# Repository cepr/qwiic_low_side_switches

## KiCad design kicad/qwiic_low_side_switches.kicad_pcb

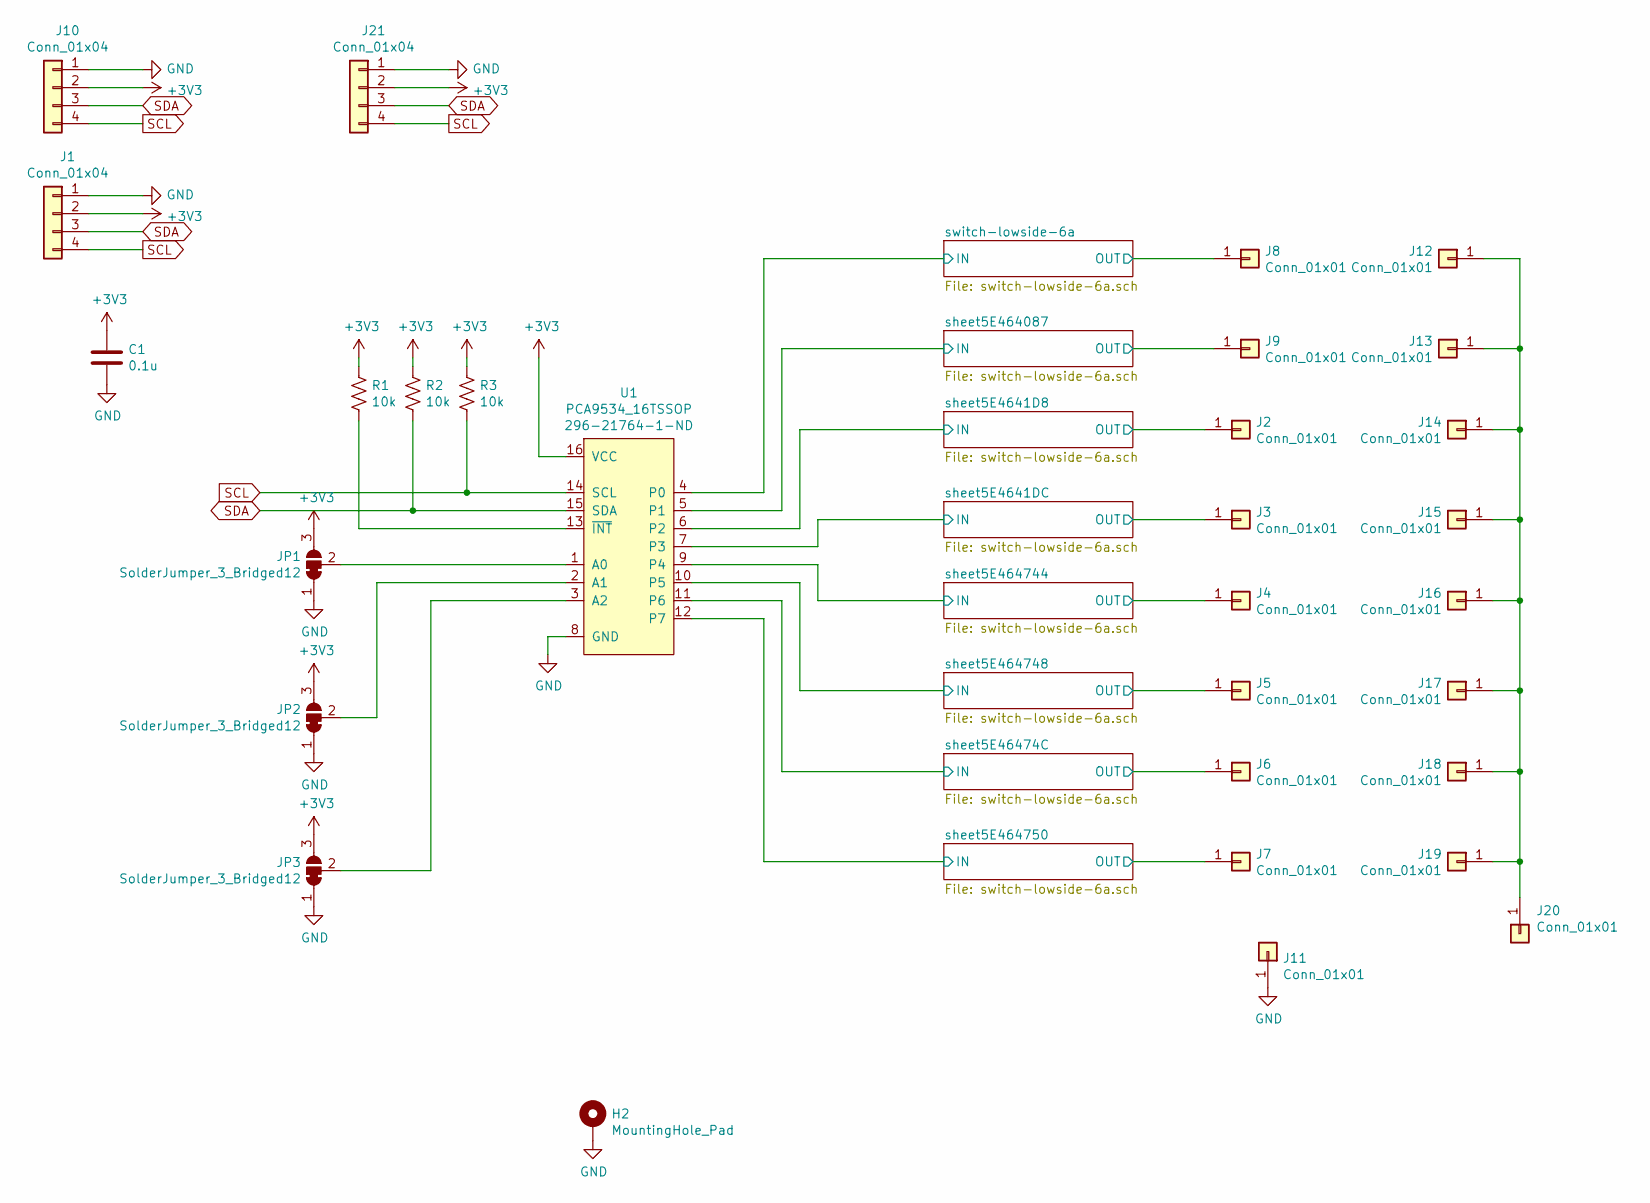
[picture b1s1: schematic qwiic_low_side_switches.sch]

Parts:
C1: 0.1u; C_0805_2012Metric_Pad1.15x1.40mm_HandSolder; DigiKey 478-6048-1-ND
H2: MountingHole_Pad; MountingHole_3.2mm_M3_Pad_Via
J1, J10: Conn_01x04; JST_SH_SM04B-SRSS-TB_1x04-1MP_P1.00mm_Horizontal; DigiKey 455-1804-1-ND
J2, J3, J4, J5, J6, J7, J8, J9, J11, J12, J13, J14, J15, J16, J17, J18, J19, J20: Conn_01x01; TestPoint_Pad_4.0x4.0mm
J21: Conn_01x04; PinSocket_1x04_P1.27mm_Vertical
JP1, JP2, JP3: SolderJumper_3_Bridged12; SolderJumper-3_P1.3mm_Bridged12_RoundedPad1.0x1.5mm_NumberL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
R1, R2, R3: 10k; R_0805_2012Metric_Pad1.15x1.40mm_HandSolder; DigiKey 311-10.0KCRCT-ND
U1: PCA9534_16TSSOP; TSSOP-16_4.4x5mm_P0.65mm; DigiKey 296-21764-1-ND

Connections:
+3V3: C1.1, J1.2, J10.2, J21.2, JP1.3 (B), JP2.3 (B), JP3.3 (B), R1.1, R2.1, R3.1, U1.16 (VCC)
/sheet5E4641D8/IN: U1.6 (P2); also elsewhere on the board
/sheet5E4641D8/OUT: J2.1; also elsewhere on the board
/sheet5E4641DC/IN: U1.7 (P3); also elsewhere on the board
/sheet5E4641DC/OUT: J3.1; also elsewhere on the board
/sheet5E46474C/IN: U1.11 (P6); also elsewhere on the board
/sheet5E46474C/OUT: J6.1; also elsewhere on the board
/sheet5E464087/IN: U1.5 (P1); also elsewhere on the board
/sheet5E464087/OUT: J9.1; also elsewhere on the board
/sheet5E464744/IN: U1.9 (P4); also elsewhere on the board
/sheet5E464744/OUT: J4.1; also elsewhere on the board
/sheet5E464748/IN: U1.10 (P5); also elsewhere on the board
/sheet5E464748/OUT: J5.1; also elsewhere on the board
/sheet5E464750/IN: U1.12 (P7); also elsewhere on the board
/sheet5E464750/OUT: J7.1; also elsewhere on the board
/switch-lowside-6a/IN: U1.4 (P0); also elsewhere on the board
/switch-lowside-6a/OUT: J8.1; also elsewhere on the board
GND: C1.2, H2.1, J1.1, J10.1, J11.1, J21.1, JP1.1 (A), JP2.1 (A), JP3.1 (A), U1.8 (GND); also elsewhere on the board
unnamed: J12.1, J13.1, J14.1, J15.1, J16.1, J17.1, J18.1, J19.1, J20.1
unnamed: JP1.2 (C), U1.1 (A0)
unnamed: JP2.2 (C), U1.2 (A1)
unnamed: JP3.2 (C), U1.3 (A2)
unnamed: R1.2, U1.13 (~INT)
SCL: J1.4, J10.4, J21.4, R3.2, U1.14 (SCL)
SDA: J1.3, J10.3, J21.3, R2.2, U1.15 (SDA)

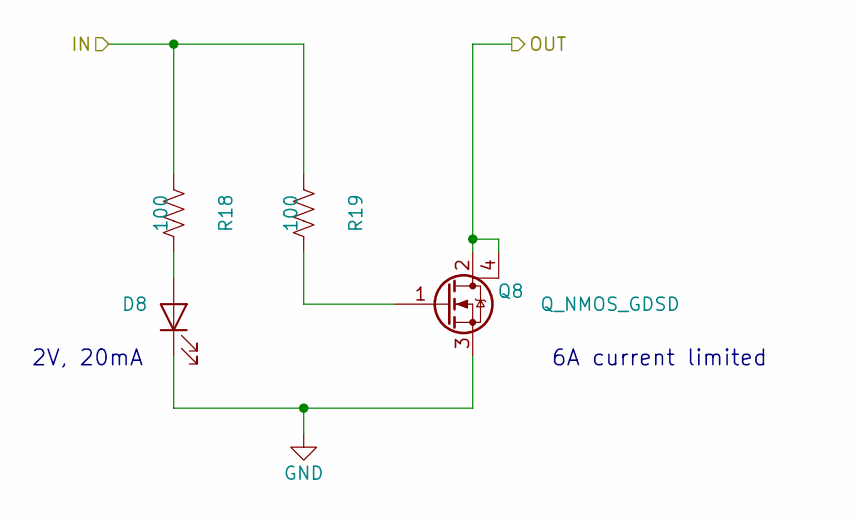
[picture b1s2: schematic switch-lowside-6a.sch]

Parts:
D1: LITEON-LTST-C170KGKT; LED_0805_2012Metric; DigiKey 160-1414-1-ND
Q1: Q_NMOS_GDSD; SOT-223; DigiKey 497-11714-1-ND
R4, R5: 100; R_0805_2012Metric_Pad1.15x1.40mm_HandSolder; DigiKey 311-100CRCT-ND

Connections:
/switch-lowside-6a/IN: R4.2, R5.2; also elsewhere on the board
/switch-lowside-6a/OUT: Q1.2 (D), Q1.4 (D); also elsewhere on the board
GND: D1.1 (K), Q1.3 (S); also elsewhere on the board
unnamed: D1.2 (A), R4.1
unnamed: Q1.1 (G), R5.1

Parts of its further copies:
D2, D3, D4, D5, D6, D7, D8: LITEON-LTST-C170KGKT; LED_0805_2012Metric; DigiKey 160-1414-1-ND
Q2, Q3, Q4, Q5, Q6, Q7, Q8: Q_NMOS_GDSD; SOT-223; DigiKey 497-11714-1-ND
R6, R7, R8, R9, R10, R11, R12, R13, R14, R15, R16, R17, R18, R19: 100; R_0805_2012Metric_Pad1.15x1.40mm_HandSolder; DigiKey 311-100CRCT-ND

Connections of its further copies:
/sheet5E4641D8/IN: R8.2, R9.2; also elsewhere on the board
/sheet5E4641D8/OUT: Q3.2 (D), Q3.4 (D); also elsewhere on the board
/sheet5E4641DC/IN: R10.2, R11.2; also elsewhere on the board
/sheet5E4641DC/OUT: Q4.2 (D), Q4.4 (D); also elsewhere on the board
/sheet5E46474C/IN: R16.2, R17.2; also elsewhere on the board
/sheet5E46474C/OUT: Q7.2 (D), Q7.4 (D); also elsewhere on the board
/sheet5E464087/IN: R6.2, R7.2; also elsewhere on the board
/sheet5E464087/OUT: Q2.2 (D), Q2.4 (D); also elsewhere on the board
/sheet5E464744/IN: R12.2, R13.2; also elsewhere on the board
/sheet5E464744/OUT: Q5.2 (D), Q5.4 (D); also elsewhere on the board
/sheet5E464748/IN: R14.2, R15.2; also elsewhere on the board
/sheet5E464748/OUT: Q6.2 (D), Q6.4 (D); also elsewhere on the board
/sheet5E464750/IN: R18.2, R19.2; also elsewhere on the board
/sheet5E464750/OUT: Q8.2 (D), Q8.4 (D); also elsewhere on the board
GND: D2.1 (K), D3.1 (K), D4.1 (K), D5.1 (K), D6.1 (K), D7.1 (K), D8.1 (K), Q2.3 (S), Q3.3 (S), Q4.3 (S), Q5.3 (S), Q6.3 (S), Q7.3 (S), Q8.3 (S); also elsewhere on the board
unnamed: D2.2 (A), R6.1
unnamed: D3.2 (A), R8.1
unnamed: D4.2 (A), R10.1
unnamed: D5.2 (A), R12.1
unnamed: D6.2 (A), R14.1
unnamed: D7.2 (A), R16.1
unnamed: D8.2 (A), R18.1
unnamed: Q2.1 (G), R7.1
unnamed: Q3.1 (G), R9.1
unnamed: Q4.1 (G), R11.1
unnamed: Q5.1 (G), R13.1
unnamed: Q6.1 (G), R15.1
unnamed: Q7.1 (G), R17.1
unnamed: Q8.1 (G), R19.1

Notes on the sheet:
2V, 20mA
6A current limited

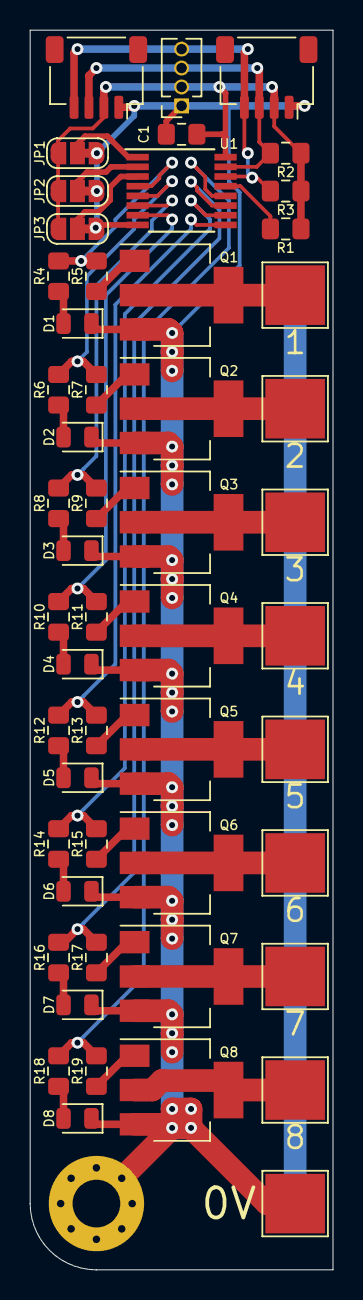
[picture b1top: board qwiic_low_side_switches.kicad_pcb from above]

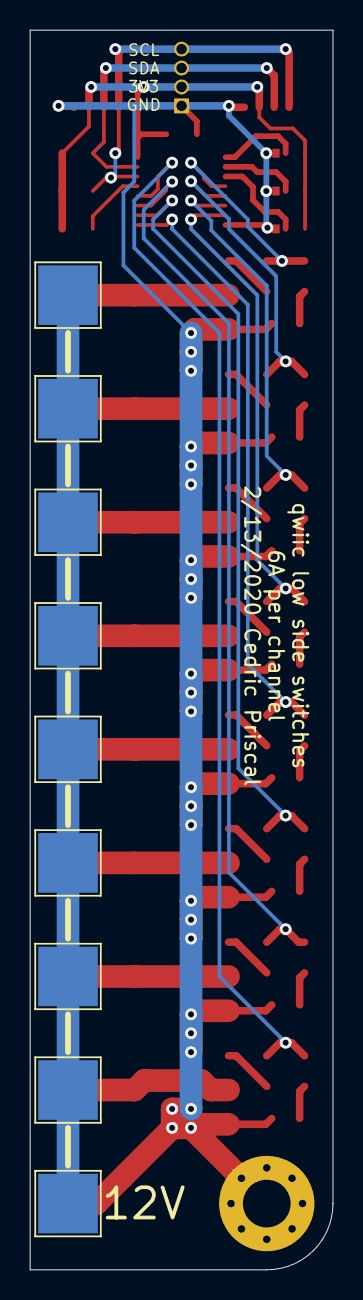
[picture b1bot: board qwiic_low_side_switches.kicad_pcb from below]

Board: 2 copper layers, 20.3 x 83.2 mm, 62 parts (9 on the bottom side), 41 nets.
